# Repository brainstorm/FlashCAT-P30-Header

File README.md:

# FlashCAT P30 Easy BGA-64 adapter

A [FlashcatUSB](https://www.embeddedcomputers.net/products/ParallelAdapters/)
(Mach1 / XPORT) parallel adapter for reading and writing **Intel / Micron
StrataFlash P30** NOR flash in the **64-ball Easy BGA** package (e.g.
`PC28F256P30T85`), using an HMILU BGA64-1.0-TP21NS 10 × 13 mm socket.
Designed in KiCad 10; rev C.

| Top | Bottom |
|---|---|
|  |  |

* 4-layer, 51 × 33 mm (same outline as the EC adapters), plugs into the Embedded Computers 56-pin dual header
* 1.8 V LDO for the P30 core (as in EC's own P30 TSOP-56 adapter), I/O and VPP
  from the programmer's VCC
* A1…A27 wired: every P30 density from 64 Mbit to 512 Mbit, plus Micron
  P30-65nm 1 Gbit / 2 Gbit (A26/A27 on the balls that are RFU on older parts)
* all SMD parts on the bottom, decoupling right at the socket power balls
* ERC / DRC / schematic-parity clean; gerbers, drill, BOM and pick-and-place
  in [`hardware/fab`](hardware/fab)

Full design notes, BOM and checks before ordering:
**[hardware/README.md](hardware/README.md)**

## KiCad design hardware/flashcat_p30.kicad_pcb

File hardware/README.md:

# FlashCAT P30 Easy BGA-64 adapter

KiCad 10 project for a FlashcatUSB (Mach1 / XPORT) parallel adapter that reads
and writes **Intel / Micron StrataFlash P30** parallel NOR in the **64-ball
Easy BGA** package (e.g. `PC28F256P30T85`, `RC28F256P30T85`; the `JS28F…`
parts are TSOP-56 and need the TSOP adapter instead), using an **HMILU
BGA64-1.0-TP21NS** open-top socket made for **10 × 13 mm** BGA-64 parts, as
discussed with Embedded Computers (thread "256P30T", Oct 2020 – Feb 2021).
Rev C; rev B used a Sensata CBG064-087G, whose nest is for 11 × 13 mm parts.

| Top (socket) | Bottom (all SMD parts) |
|---|---|
|  |  |
|  |  |

| Side | Decoupling at the socket balls (bottom) |
|---|---|
|  |  |

Schematic as PDF: [`fab/docs/schematic.pdf`](fab/docs/schematic.pdf) ·
Gerbers: [`fab/flashcat_p30-gerbers.zip`](fab/flashcat_p30-gerbers.zip)

```
hardware/
  flashcat_p30.kicad_pro / .kicad_sch / .kicad_pcb   the project
  lib/flashcat_p30.kicad_sym                         P30 socket, EC header, LDO, R, C, power symbols
  lib/flashcat_p30.pretty/HMILU_BGA64-1.0-TP21NS     socket footprint, pads named with P30 ball names
  lib/flashcat_p30.3dshapes/HMILU_BGA64-1.0-TP21NS.step  socket 3D model (built from the HMILU drawing)
  fab/                                               gerbers (+zip), drill, BOM, CPL, PDFs
  renders/                                           3D renders, schematic preview, sheet view
  tools/                                             generators + checks (source of truth: design.py)
```

## What the board does

| P30 ball(s) | Signal | Connected to |
|---|---|---|
| A1…A25 | address (A1 = LSB, word address) | EC header **A1…A25** (header A0 unused) |
| B8 / H1 | RFU on 130 nm parts; **A26 / A27** on Micron P30-65nm 1 / 2 Gbit | EC header **A26/RB2 / A27/RB1** |
| DQ0…DQ15 | data | EC header DQ0…DQ15 |
| CE#, OE#, WE# | control | EC header CE0, OE, WE (driven directly, no pull-ups) |
| RST# | reset | 10k to VCC + 100 nF to GND (~1 ms power-on reset) |
| WP# | write protect | tied to header VCC (lock-down disabled) |
| ADV#, CLK | sync-burst inputs | GND (asynchronous mode, per datasheet) |
| WAIT | wait/ready | EC header **RB0**, 4.7k pull-up to VCC |
| RFU (E8, F1, G2) | – | open |
| VCC ×2 | core 1.7–2.0 V | **+1V8** from U2 (TLV75518) – the LDO feeds only these |
| VPP | program/erase supply | header **VCC** (3.3 V) |
| VCCQ ×3 | I/O 1.7–3.6 V | header **VCC** (header VIO unused) |
| VSS ×4 | ground | GND |

Why these choices — cross-checked against the author's own **TSOP-56 Type-D**
adapter ("Supports P30 and P33 Strataflash devices such as 28F256P30",
schematic [`SCM_TSOP56_D.png`](https://www.embeddedcomputers.net/products/ParallelAdapters/SCM_TSOP56_D.png) on the [EC parallel adapters page](https://www.embeddedcomputers.net/products/ParallelAdapters/)):

| | EC TSOP-56 Type-D (P30) | this board |
|---|---|---|
| Core VCC | **MIC5504 1.8 V LDO** from header VCC, 3 × 1 µF | TLV75518 1.8 V LDO (same SOT-23-5 pinout; MIC5504-1.8YM5 is a drop-in) |
| VCCQ | header VCC | header VCC |
| Header VIO | unused | unused |
| WAIT | → RB0, 4.7k pull-up to VCC | same |
| CLK, ADV# | GND | GND |
| WP# | tied to VCC | tied to VCC |
| RST# | tied to VCC | 10k pull-up to VCC + 100 nF (~1 ms power-on reset) |
| TSOP pin 13 / pin 28 | wired to header A27/RB1 and A26/RB2 (see note) | Easy BGA B8 → A26/RB2, H1 → A27/RB1 (same idea) |
| VPP | VCC rail | header VCC |
| CE#, WE# pull-ups | none | none |
| Address | P30 A1 → header A1/CE2 … A25 → A25/RB3 | same, plus A26/A27 |

* **Verified in the Type-D schematic:** header VCC (pin 28) → MIC5504 VIN and
  EN, VOUT (P$5) → C3 1 µF → TSOP pin 33 **VCC**, part marked "1.8V LDO".
  Note: on that drawing TSOP pin 13 is labelled `VCC_A27` and routed to
  header A27/RB1, and pin 28 to header A26/RB2. That matches Micron's
  **P30-65nm** TSOP pinout (512 Mbit–1 Gbit): pin 28 is **A26** there (VSS on
  the 130 nm parts) and pin 13 became RFU (VCC on 130 nm). The Easy BGA
  equivalent is below.
* **Is the LDO needed? Yes.** None of the other EC adapters carry a regulator
  because they are all for 3 V (or 5 V) core parts; the only adapter on the
  page with an LDO is the P30 one, for exactly the reason below. (The other
  small ICs on those schematics are a VPP load switch on DIP-40 and
  push-pull/open-drain MOSFETs on BGA-153, not regulators.)

* **Addressing**: the FlashcatUSB firmware/software drives the header in x16 NOR
  mode as *"Addressing is done A1-A27 (WORD ADDR)"* (`Parallel_NOR_NAND.vb`,
  `E_EXPIO_WRADDR.Parallel_X16`). P30 names its LSB `A1`, so `An` → header
  `An` — the "same pin connection as the TSOP56" the author mentioned.
  A25 is wired so 512 Mbit dual-die P30 parts work too.
* **Micron P30-65nm (1 Gbit / 2 Gbit)** uses the same Easy BGA ballout but
  puts **A26 on ball B8** and **A27 on ball H1** (die select on the 2 Gbit
  dual-die part), balls that are RFU on the 130 nm Intel/Numonyx datasheet.
  Both are wired straight to header A26/RB2 and A27/RB1 so `PC28F00AP30…`
  and `PC28F00BP30…` parts work. On 130 nm parts those balls are unused
  inside the package, so the programmer driving them is expected to be
  harmless (the datasheet asks to treat RFU as do-not-connect, and EC's TSOP
  Type-D adapter makes the same trade-off). Needs FlashcatUSB to know the
  part; 65 nm parts also need ≥ 300 µs from VCC valid to RST# high, which
  the ~1 ms RC covers.
* **Core voltage**: P30 `VCC` is 1.7–2.0 V with an **absolute maximum of 2.5 V**,
  while the header VCC runs at 3.3 V for these adapters (the author's MIC5504
  needs ≥ 2.5 V in, so their design assumes 3.3 V too). Wiring `VCC` straight
  to the header would destroy the chip. U2 (TLV755P, 1.45–5.5 V input) was
  kept over the MIC5504 because it also survives a 1.8 V programmer setting:
  it just drops out and passes ~1.78 V through.
* **VPP** goes to header VCC (3.3 V), like the author's adapter. VPPL is
  0.9–3.6 V, but program/erase timings are specified at the higher end, and
  this keeps the LDO dedicated to the core VCC balls. The header's VPP pin (which can carry 12 V for old EPROMs)
  is deliberately left unconnected.

## Mechanical / geometry

* Board: 51 × 33 mm, 4 layers, 1.6 mm, rounded corners: the same outline as
  Embedded Computers' own adapters (measured from their TSOP-56 Type-D and
  BGA-64 board photos against the 2.00 mm header pitch, ≈ 51 × 33 mm),
  headers along the short edges. The 26 × 30 mm socket body fits inside it.
  Stack: F.Cu signals + GND pour · In1 solid GND plane · In2 signals + VCC
  pour · B.Cu signals + GND pour.
* BGA escape is a fixed, hand-planned fanout (`tools/fanout.py`): rings 1+2 on
  F.Cu, ring 3 on B.Cu, the centre balls on In2 (VCCQ D5 is linked to its
  VCCQ neighbour D6 instead of escaping), one 0.127 mm track per channel;
  each escape exits on the side facing its header (data → J1, address → J2);
  B.Cu channels next to A4/A6/H3/G4 are kept free for the bottom decap traces,
  and a locked B.Cu link joins the two VCCQ cap groups onto one VCC via. Balls
  that leave the top layer (inner escapes, GND balls, decap balls) do so
  through a **0.3/0.5 mm via in the centre of their pad** (23 pads), which
  has to be **resin filled and copper capped** (see fabrication spec); GND
  balls drop straight into the In1 plane that way. D3 (A11) and F4 (DQ11)
  escape sideways towards their header pins, and A2, DQ11, DQ12 and WAIT are
  pre-routed by hand (`design.PREROUTES`): Freerouting otherwise walled
  their header pins in. The rest was autorouted with Freerouting and
  cleaned up (dangling stubs and pad vias it made redundant removed).
* EC 56-pin header: two 2×14, 2.00 mm male headers mounted from the **bottom**
  (plastic spacer between adapter and programmer), left columns 42.00 mm
  apart, positions per [`EC_56P_HEADER.png`](https://www.embeddedcomputers.net/products/ParallelAdapters/EC_56P_HEADER.png). Top-silk "GND" and "A0" mark the
  first pins; all silkscreen reads the same way as the programmer's. As on
  EC's own adapters (TSOP-56 Type-D, BGA-64 photos on their
  [parallel adapters page](https://www.embeddedcomputers.net/products/ParallelAdapters/)),
  each header has a top-silk outline box and two solid "◄" triangles sit on
  the inner side of the data header (J1) at its first and last row, to line
  the adapter up with the matching mark on the FlashcatUSB.
* **Socket:** footprint per the **HMILU drawing 007-BGA-1.0-64-10X13-B-01
  rev A** ("PCB Pattern (TOP View)"), placed exactly as drawn:
  * 64 × Ø0.55 mm **solid SMD pads** for the solderless double-sided spring
    contacts: mask opening, **no solder paste**. The 8×8 grid is offset from
    the socket centre: left column and top row 3.25 mm from the centre lines,
    right column and bottom row 3.75 mm.
  * 4 locator pins, NPTH at (±5.6, ±10.0) mm: Ø1.75 at the A1 corner
    (top-right), Ø1.45 for the other three, which polarises the socket.
    The drawing asks for +0.05/−0 on Ø1.4 / Ø1.7 pins; they are drilled
    1.53 / 1.83 mm so the fab's −0.08 mm hole tolerance (JLCPCB: +0.13/−0.08)
    can never make them smaller than the drawing's minimum (worst case
    ~0.13 mm of play, well inside the Ø0.55 pads for the 0.17 mm contacts).
  * 4 × Ø2.00 mm NPTH fixing holes at (±10.6, ±11.1) mm for the socket screws.
  * Bottom-side courtyards keep parts 2.3 mm clear of the screw holes and
    1.3 mm clear of the locator pin tips (3.4 mm long, ~1.8 mm below the board).
* **Socket orientation:** the IC sits with its 13 mm side along X and pin
  **A1 at the top-right** (silk triangle outside the socket body). Ball
  letters A–H run right → left, numbers 1–8 top → bottom (the datasheet top
  view turned 90° clockwise), so the address-heavy columns (A–D) face the
  address header J2 and the data columns (E–H) face J1.
* No silkscreen inside the socket body on the top side, so the socket base
  sits flat on the solder mask.

## ⚠ Check before ordering

1. **Socket fixing screws.** The drawing gives 4 × Ø2.00 mm fixing holes
   but not the screw. Check the screws that come with your socket and how
   they fasten (into the socket body, or with nuts under the board), and
   widen the holes if they need clearance. Their heads sit on the bottom
   side, inside the courtyards described above.
2. **Header orientation vs. your programmer.** With your working TSOP56
   adapter, check continuity: TSOP56 pin 29 (P30 A1) should go to header pin
   "A1/CE2" (J2, left column, 2nd row), and pin 30 (CE#) to "CE0". This
   confirms both the word-address convention and the top-view pin order used here.
3. **Programmer voltage.** Select the P30 device (28F256P30T) in FlashcatUSB
   and run it the same way as the TSOP-56 Type-D adapter (3.3 V). I/O runs at
   header VCC, like the author's adapter.
4. **Do not use EC's own "BGA-64 EasyBGA (28 series)" adapter for P30.** Its
   published pinout ([`BGA64_EasyBGA_Pinout.png`](https://www.embeddedcomputers.net/products/ParallelAdapters/BGA64_EasyBGA_Pinout.png)) is the J3-style ballout
   (VPEN, STS, BYTE#, CE0–CE2, RP#): it powers the core from 3 V, leaves
   P30's ADV#/CLK/VCCQ(D5, D6) balls on RFU pins, and would over-voltage a P30
   core. That is why this custom board is needed.
5. **Clearance under the board.** The bottom carries the two headers plus all
   SMD parts (0603 and a SOT-23-5, ≤ 1.45 mm tall), the socket screw heads and
   the locator pin tips (~1.8 mm), inside the header spacer height; check
   nothing tall on the programmer sits under the middle of the adapter.
6. **512 Mbit parts are 1.30 mm tall** (1.20 mm for smaller densities); the
   socket drawing shows a 1.2 mm IC. Check the cover still clamps a 512 Mbit
   part properly.

## Bill of materials

| Ref | Qty | Part | Notes |
|---|---|---|---|
| U1 | 1 | HMILU **BGA64-1.0-TP21NS** BGA-64 1.0 mm socket, 10 × 13 mm | solderless: screwed onto the board after assembly; not in the CPL. 3D model in `lib/flashcat_p30.3dshapes/` |
| J1, J2 | 2 | 2×14 male header, **2.00 mm** pitch (e.g. Samtec TMM-114-01-G-D) | mount on bottom |
| U2 | 1 | TI **TLV75518PDBVR** (SOT-23-5) | 1.8 V LDO, 1.45 V min input; alt. Microchip MIC5504-1.8YM5 (same pinout, needs ≥ 2.5 V in) |
| C1, C2 | 2 | 1 µF 25 V X5R 0603 (GRM188R61E105KA12D) | LDO in / out, either side of U2 |
| C3 | 1 | 10 µF 10 V X5R 0603 (GRM188R61A106KE69D) | **bottom**, at ball A4 (VPP, header VCC) |
| C5, C6 | 2 | 100 nF 16 V X7R 0603 (GRM188R71C104KA01D) | **bottom**, at balls A6 / H3 (VCC, +1V8) |
| C4, C7 | 2 | 10 µF + 100 nF 0603 | **bottom**, at balls D5/D6 (VCCQ) |
| C8 | 1 | 100 nF 0603 | **bottom**, at ball G4 (VCCQ) |
| C9 | 1 | 100 nF 0603 | RST# power-on RC |
| R1 | 1 | 10 kΩ 1 % 0603 (RC0603FR-0710KL) | RST# pull-up (with C9: power-on reset) |
| R2 | 1 | 4.7 kΩ 1 % 0603 (RC0603FR-074K7L) | WAIT → RB0 pull-up |

**All SMD parts are on the bottom side** (single-sided SMD assembly; the top
carries only the socket). The socket decoupling caps (C3–C8) sit 1–2 mm
from their VCC/VCCQ/VPP balls, each with its own short trace from the ball
and its own GND via into the In1 plane; the LDO (U2) with C1/C2, the
WAIT pull-up and the RST# RC sit in the strips above/below the socket. Reflow
the bottom, hand-solder the headers, then screw the socket on (no solder on
its pads). `fab/assembly/`
has a generic BOM plus JLCPCB-style `bom_jlc.csv` / `cpl_jlc.csv`; placement
coordinates are relative to the socket centre (board aux origin). Add LCSC
part numbers for your assembler before ordering. Check CPL rotations in the
assembler's preview.

## Fabrication spec

| Item | Value | Source |
|---|---|---|
| Layers / material | 4 layers, FR-4, 1.6 mm, 1 oz outer copper | design choice |
| Track / space | min 0.127 / 0.127 mm (power 0.2–0.3 mm) | design choice; JLCPCB multilayer minimum is 0.09 / 0.09 mm [1] |
| Vias | 0.3 mm drill / 0.5 mm pad, min via-to-via hole gap on the board 0.37 mm | JLCPCB: via ≥ 0.15/0.25 mm, via hole-to-hole ≥ 0.2 mm [1] |
| Socket pads | 64 × Ø0.55 mm solid SMD pads, mask open, **no paste** | HMILU drawing ("64-Ø0.55 实心焊盘", contact tip detail) |
| **Via-in-pad** | 23 socket pads have a 0.3/0.5 mm via in their centre: these must be **epoxy filled and copper capped** | design choice (see below); JLCPCB: "Vias can be placed within BGA pads using filled and plated-over vias" [1] |
| Surface finish | **ENIG** | design choice: flat pads for the spring contacts (HASL leaves domed pads) |
| Locator holes | NPTH 3 × Ø1.53, 1 × Ø1.83 mm | HMILU drawing (Ø1.45 / Ø1.75 +0.05/−0) + JLCPCB hole tolerance +0.13/−0.08 mm [1] |
| Fixing holes | NPTH 4 × Ø2.00 mm | HMILU drawing |
| Silkscreen | text ≥ 1.0 mm high, ≥ 0.15 mm stroke | JLCPCB legend minimum [1] |

[1] JLCPCB PCB capabilities, https://jlcpcb.com/capabilities/pcb-capabilities
(checked 2026-10-03).

**Why via-in-pad (design choice, not from the HMILU drawing).** The drawing
only defines the pad pattern. The pads are SMD, so balls that cannot escape
on the top layer (inner balls, GND, decoupled power balls) need a via; it
was put in the pad centre because the 1.0 mm grid has no room for
dog-bone vias next to every inner pad. A filled and capped via leaves a flat
pad; an open or merely tented via would leave a hole or dimple under the
spring contact. Confirm with HMILU / your reseller that filled vias under
the contacts are fine if in doubt.

### Ordering checklist (JLCPCB)

1. Upload `fab/flashcat_p30-gerbers.zip` (Gerbers + PTH/NPTH Excellon).
2. 4 layers, 1.6 mm, **ENIG**, 1 oz outer copper; via size 0.3/0.5 mm.
3. **Via covering: "Epoxy Filled & Capped"** (via-in-pad). JLCPCB's page
   lists it as the default for 6-layer and above; for a 4-layer order check
   that the option is offered and selected, otherwise add a remark or
   choose a fab that does it. Do **not** order with tented or open vias.
4. Leave the NPTH sizes as drawn (no "hole size compensation" remark needed).
5. Assembly (optional): bottom side only, `fab/assembly/bom_jlc.csv` +
   `cpl_jlc.csv`; the socket (U1) is not assembled, the headers are
   hand-soldered. Check part rotations in the assembler's preview.

## Verification status (rev C)

`tools/verify.py`: ball/header mapping 0 errors · ERC 0 · DRC 0 violations,
0 unconnected (all severities) · schematic ↔ PCB parity 0.

## Regenerating

```
cd hardware/tools
python3 gen_libs.py     # symbols + socket footprint (references the 3D model)
../build/cqenv/bin/python make_socket_3d.py   # socket STEP model (CadQuery, Python 3.12 venv)
python3 gen_pro.py      # project, rules, net classes
python3 gen_sch.py      # schematic
python3 gen_pcb.py      # placement, nets, planes, silk (from schematic netlist)
python3 route.py        # fanout + Freerouting 2.4.1 (Java 25; FR_VERSION=2.1.0 for Java 21)
                        #   + stub trim + pours + fill, retries until 0 unconnected
python3 center.py       # move board to the middle of the A4 sheet, aux/grid origin = socket centre
python3 verify.py       # mapping + ERC + DRC with schematic parity
python3 make_fab.py     # gerbers, drill, BOM, CPL, PDFs
```

`design.py` is the single source of truth for the ballout, header pinout,
socket geometry and nets. Once hand-edited in KiCad, the `.kicad_*` files
become the master copy and the generators should not be re-run.

## 3D model of the socket

No vendor model is published for the BGA64-1.0-TP21NS, so
`tools/make_socket_3d.py` builds a simplified STEP from the HMILU drawing's
top, front-section and isometric views: a base with four corner towers
(3.3 mm slab, towers to 7.5 mm) and the 10 × 13 mm IC holder between them; a
26 × 30 mm cover (10.8–17.5 mm, cover up) with an 18 × 14 mm funnel window,
countersunk corner holes and a skirt in the middle of each side that drops
between the towers (with the guide slot and pin on the 30 mm faces); coil
springs on the towers around the corner screw posts; the two clamp arms
(levers on pins beside the IC holder, hook tips resting on the chip's 13 mm
edges, as in the drawing's top and side views); 64 contact blades down
to the pads and the four locator pins (3.4 mm). Hole, pin and contact
positions come from `design.py`, so they match the footprint exactly;
proportions the drawing does not dimension were measured from it. It is for
fit/clearance checks and renders, not a manufacturer-accurate model.

## References

* Intel StrataFlash Embedded Memory (P30) datasheet, order 306666 –
  [PDF](https://www.dataman.com/media/datasheet/Intel/P30Family.pdf)
* Micron Parallel NOR Flash Embedded Memory (P30-65nm) 512Mb/1Gb/2Gb
  datasheet (Easy BGA ballout with A26/A27) –
  [PDF](https://www.mouser.com/datasheet/2/12/P30_512M_Datasheet-1920645.pdf)
* HMILU BGA64-1.0-TP21NS BGA-64 socket, drawing
  007-BGA-1.0-64-10X13-B-01 rev A (from the socket vendor; not redistributed
  here)
* Embedded Computers FlashcatUSB parallel adapters (EC 56-pin header, TSOP-56
  Type-D P30 adapter) – [embeddedcomputers.net](https://www.embeddedcomputers.net/products/ParallelAdapters/)

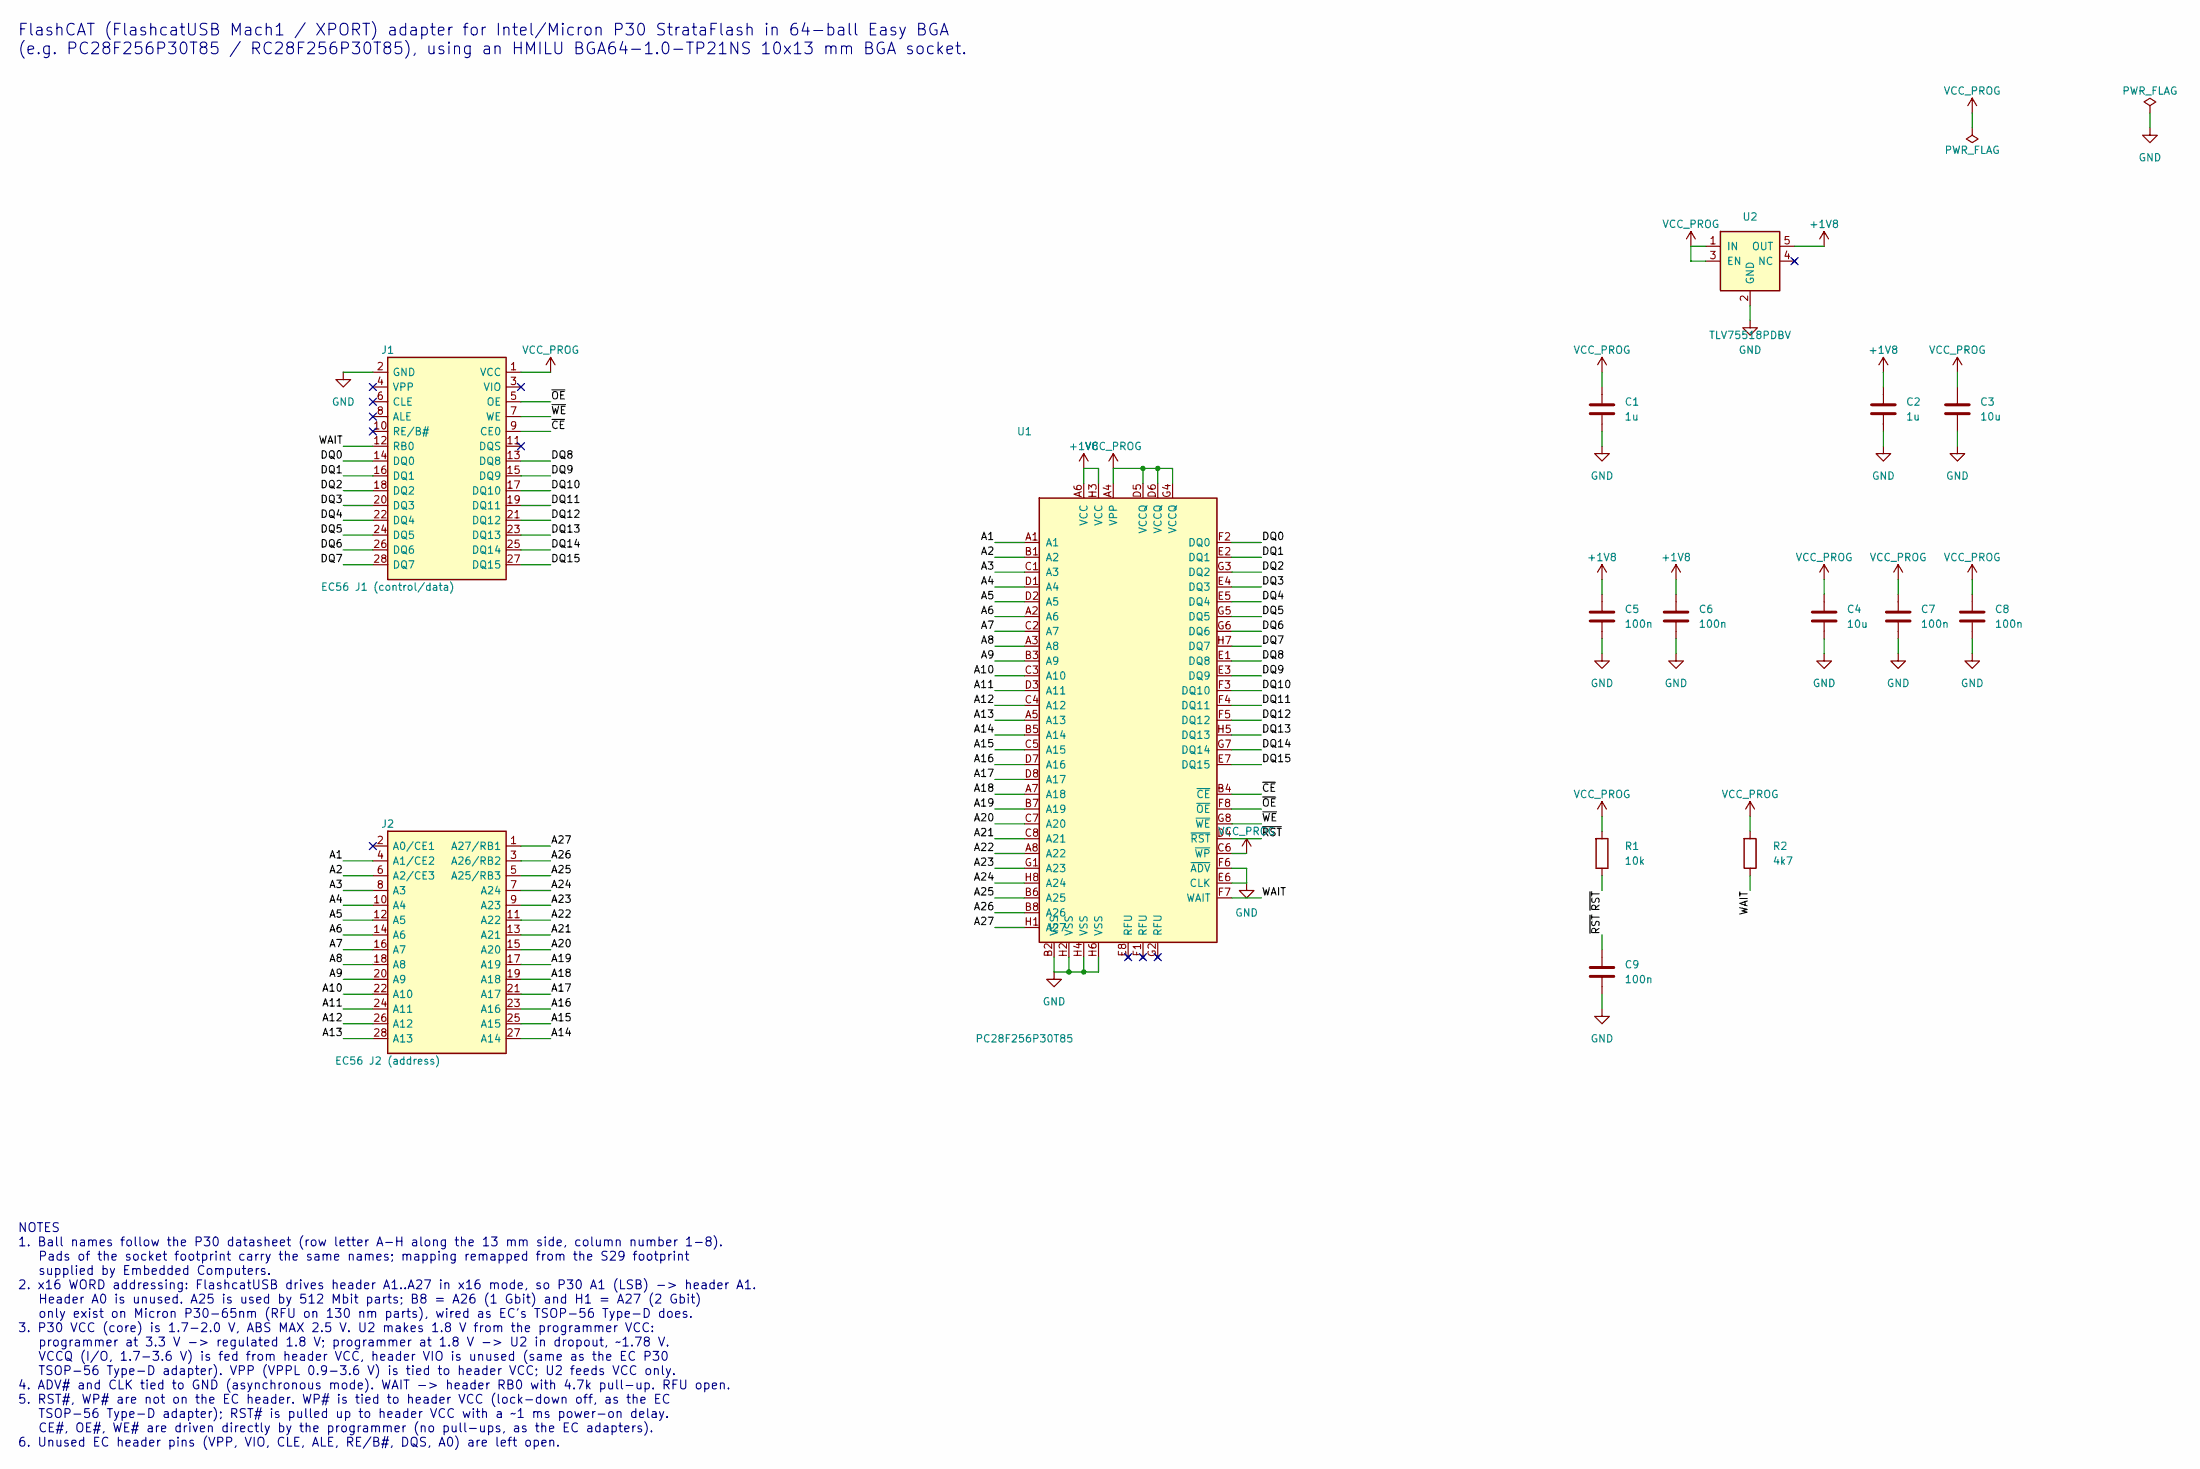
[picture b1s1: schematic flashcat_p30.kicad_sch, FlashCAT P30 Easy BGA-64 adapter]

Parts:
C1, C2: 1u; C_0603_1608Metric; MPN GRM188R61E105KA12D
C3, C4: 10u; C_0603_1608Metric; MPN GRM188R61A106KE69D
C5, C6, C7, C8, C9: 100n; C_0603_1608Metric; MPN GRM188R71C104KA01D
J1: EC56 J1 (control/data); PinHeader_2x14_P2.00mm_Vertical; MPN Samtec TMM-114-01-G-D (or any 2x14 2.00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
J2: EC56 J2 (address); PinHeader_2x14_P2.00mm_Vertical; MPN Samtec TMM-114-01-G-D (or any 2x14 2.00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
R1: 10k; R_0603_1608Metric; MPN RC0603FR-0710KL
R2: 4k7; R_0603_1608Metric; MPN RC0603FR-074K7L
U1: PC28F256P30T85; HMILU_BGA64-1.0-TP21NS; MPN BGA64-1.0-TP21NS
U2: TLV75518PDBV; SOT-23-5; MPN TLV75518PDBVR

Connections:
+1V8: C2.1, C5.1, C6.1, U1.A6 (VCC), U1.H3 (VCC), U2.5 (OUT)
/A1: J2.4 (A1/CE2), U1.A1
/A2: J2.6 (A2/CE3), U1.B1 (A2)
/A3: J2.8 (A3), U1.C1 (A3)
/A4: J2.10 (A4), U1.D1 (A4)
/A5: J2.12 (A5), U1.D2 (A5)
/A6: J2.14 (A6), U1.A2 (A6)
/A7: J2.16 (A7), U1.C2 (A7)
/A8: J2.18 (A8), U1.A3 (A8)
/A9: J2.20 (A9), U1.B3 (A9)
/A10: J2.22 (A10), U1.C3 (A10)
/A11: J2.24 (A11), U1.D3 (A11)
/A12: J2.26 (A12), U1.C4 (A12)
/A13: J2.28 (A13), U1.A5 (A13)
/A14: J2.27 (A14), U1.B5 (A14)
/A15: J2.25 (A15), U1.C5 (A15)
/A16: J2.23 (A16), U1.D7 (A16)
/A17: J2.21 (A17), U1.D8 (A17)
/A18: J2.19 (A18), U1.A7 (A18)
/A19: J2.17 (A19), U1.B7 (A19)
/A20: J2.15 (A20), U1.C7 (A20)
/A21: J2.13 (A21), U1.C8 (A21)
/A22: J2.11 (A22), U1.A8 (A22)
/A23: J2.9 (A23), U1.G1 (A23)
/A24: J2.7 (A24), U1.H8 (A24)
/A25: J2.5 (A25/RB3), U1.B6 (A25)
/A26: J2.3 (A26/RB2), U1.B8 (A26)
/A27: J2.1 (A27/RB1), U1.H1 (A27)
/DQ0: J1.14 (DQ0), U1.F2 (DQ0)
/DQ1: J1.16 (DQ1), U1.E2 (DQ1)
/DQ2: J1.18 (DQ2), U1.G3 (DQ2)
/DQ3: J1.20 (DQ3), U1.E4 (DQ3)
/DQ4: J1.22 (DQ4), U1.E5 (DQ4)
/DQ5: J1.24 (DQ5), U1.G5 (DQ5)
/DQ6: J1.26 (DQ6), U1.G6 (DQ6)
/DQ7: J1.28 (DQ7), U1.H7 (DQ7)
/DQ8: J1.13 (DQ8), U1.E1 (DQ8)
/DQ9: J1.15 (DQ9), U1.E3 (DQ9)
/DQ10: J1.17 (DQ10), U1.F3 (DQ10)
/DQ11: J1.19 (DQ11), U1.F4 (DQ11)
/DQ12: J1.21 (DQ12), U1.F5 (DQ12)
/DQ13: J1.23 (DQ13), U1.H5 (DQ13)
/DQ14: J1.25 (DQ14), U1.G7 (DQ14)
/DQ15: J1.27 (DQ15), U1.E7 (DQ15)
/WAIT: J1.12 (RB0), R2.2, U1.F7 (WAIT)
/~CE: J1.9 (CE0), U1.B4 (~CE)
/~OE: J1.5 (OE), U1.F8 (~OE)
/~RST: C9.1, R1.2, U1.D4 (~RST)
/~WE: J1.7 (WE), U1.G8 (~WE)
GND: C1.2, C2.2, C3.2, C4.2, C5.2, C6.2, C7.2, C8.2, C9.2, J1.2 (GND), U1.B2 (VSS), U1.E6 (CLK), U1.F6 (~ADV), U1.H2 (VSS), U1.H4 (VSS), U1.H6 (VSS), U2.2 (GND)
VCC_PROG: C1.1, C3.1, C4.1, C7.1, C8.1, J1.1 (VCC), R1.1, R2.1, U1.A4 (VPP), U1.C6 (~WP), U1.D5 (VCCQ), U1.D6 (VCCQ), U1.G4 (VCCQ), U2.1 (IN), U2.3 (EN)

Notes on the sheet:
FlashCAT (FlashcatUSB Mach1 / XPORT) adapter for Intel/Micron P30 StrataFlash in 64-ball Easy BGA (e.g. PC28F256P30T85 / RC28F256P30T85), using an HMILU BGA64-1.0-TP21NS 10x13 mm BGA socket.
NOTES 1. Ball names follow the P30 datasheet (row letter A-H along the 13 mm side, column number 1-8). Pads of the socket footprint carry the same names; mapping remapped from the S29 footprint supplied by Embedded Computers. 2. x16 WORD addressing: FlashcatUSB drives header A1..A27 in x16 mode, so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

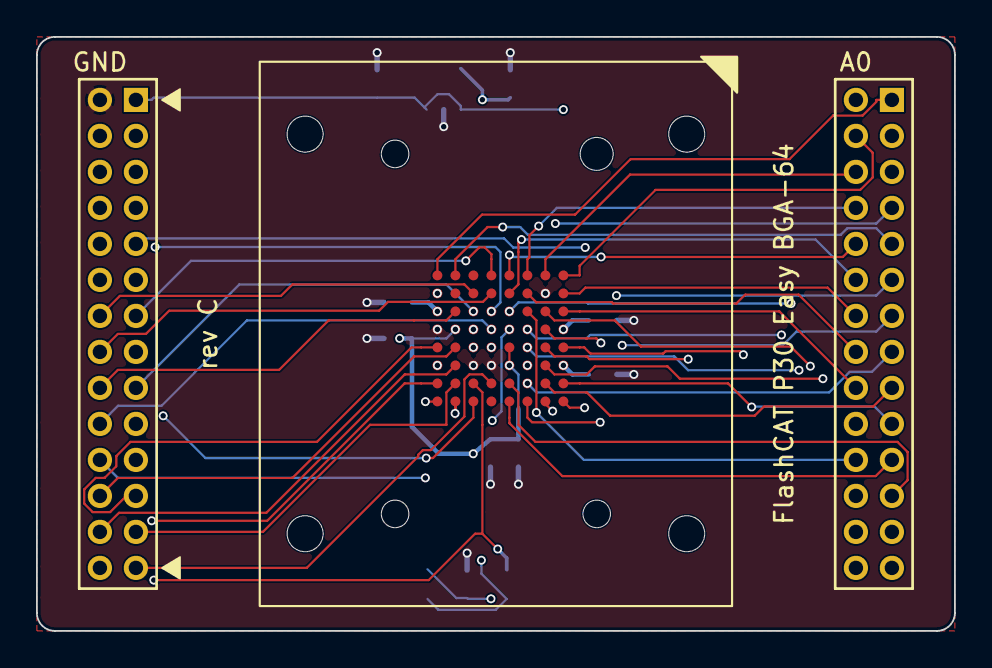
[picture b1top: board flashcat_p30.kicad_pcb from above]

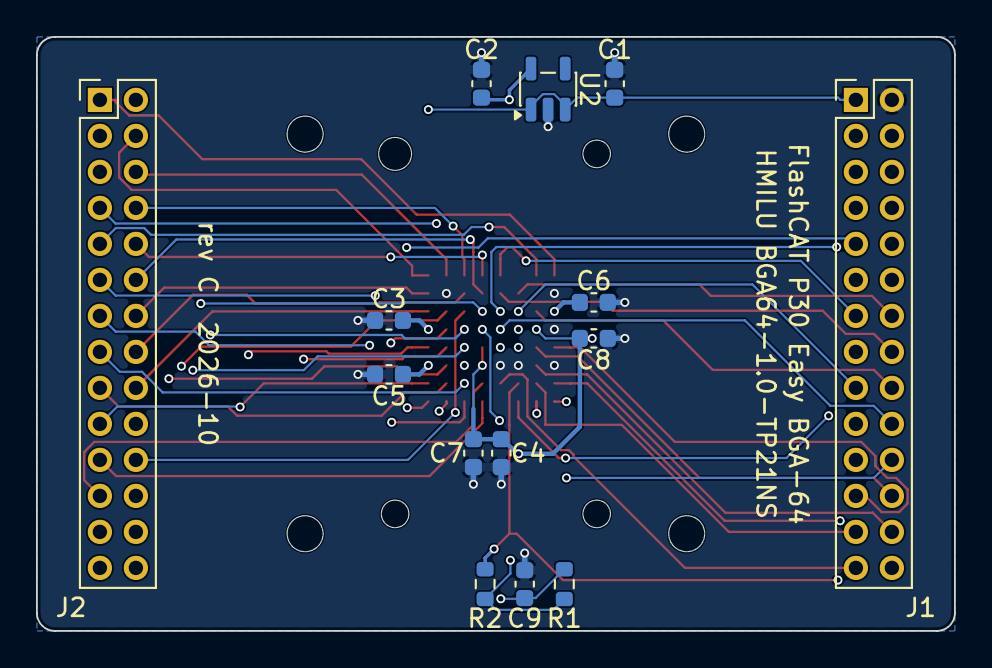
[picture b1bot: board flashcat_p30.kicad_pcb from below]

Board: 4 copper layers, 51.0 x 33.0 mm, 15 parts (14 on the bottom side), 51 nets.

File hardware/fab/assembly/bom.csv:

"Reference","Value","Footprint","MPN","Manufacturer","Qty"
"C1,C2","1u","Capacitor_SMD:C_0603_1608Metric","GRM188R61E105KA12D","","2"
"C3,C4","10u","Capacitor_SMD:C_0603_1608Metric","GRM188R61A106KE69D","","2"
"C5,C6,C7,C8,C9","100n","Capacitor_SMD:C_0603_1608Metric","GRM188R71C104KA01D","","5"
"J1","EC56 J1 (control/data)","Connector_PinHeader_2.00mm:PinHeader_2x14_P2.00mm_Vertical","Samtec TMM-114-01-G-D (or any 2x14 2.00 mm male header)","","1"
"J2","EC56 J2 (address)","Connector_PinHeader_2.00mm:PinHeader_2x14_P2.00mm_Vertical","Samtec TMM-114-01-G-D (or any 2x14 2.00 mm male header)","","1"
"R1","10k","Resistor_SMD:R_0603_1608Metric","RC0603FR-0710KL","","1"
"R2","4k7","Resistor_SMD:R_0603_1608Metric","RC0603FR-074K7L","","1"
"U1","PC28F256P30T85","flashcat_p30:HMILU_BGA64-1.0-TP21NS","BGA64-1.0-TP21NS","HMILU","1"
"U2","TLV75518PDBV","Package_TO_SOT_SMD:SOT-23-5","TLV75518PDBVR","Texas Instruments","1"
